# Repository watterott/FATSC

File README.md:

# FATSC
FATSC (FAT Storage Controller) is a SD/USB coprocessor to connect USB memory sticks or SD cards to a microcontroller.

* USB-Host MSD/MSC port
* SD-Card interface
* Real-Time-Clock (RTC)
* FAT/FAT32 file system
* Based on a ST STM32F205 ARM microcontroller
* ALFAT compatible pinout and commands
* **[Documentation on learn.watterott.com](https://learn.watterott.com)**

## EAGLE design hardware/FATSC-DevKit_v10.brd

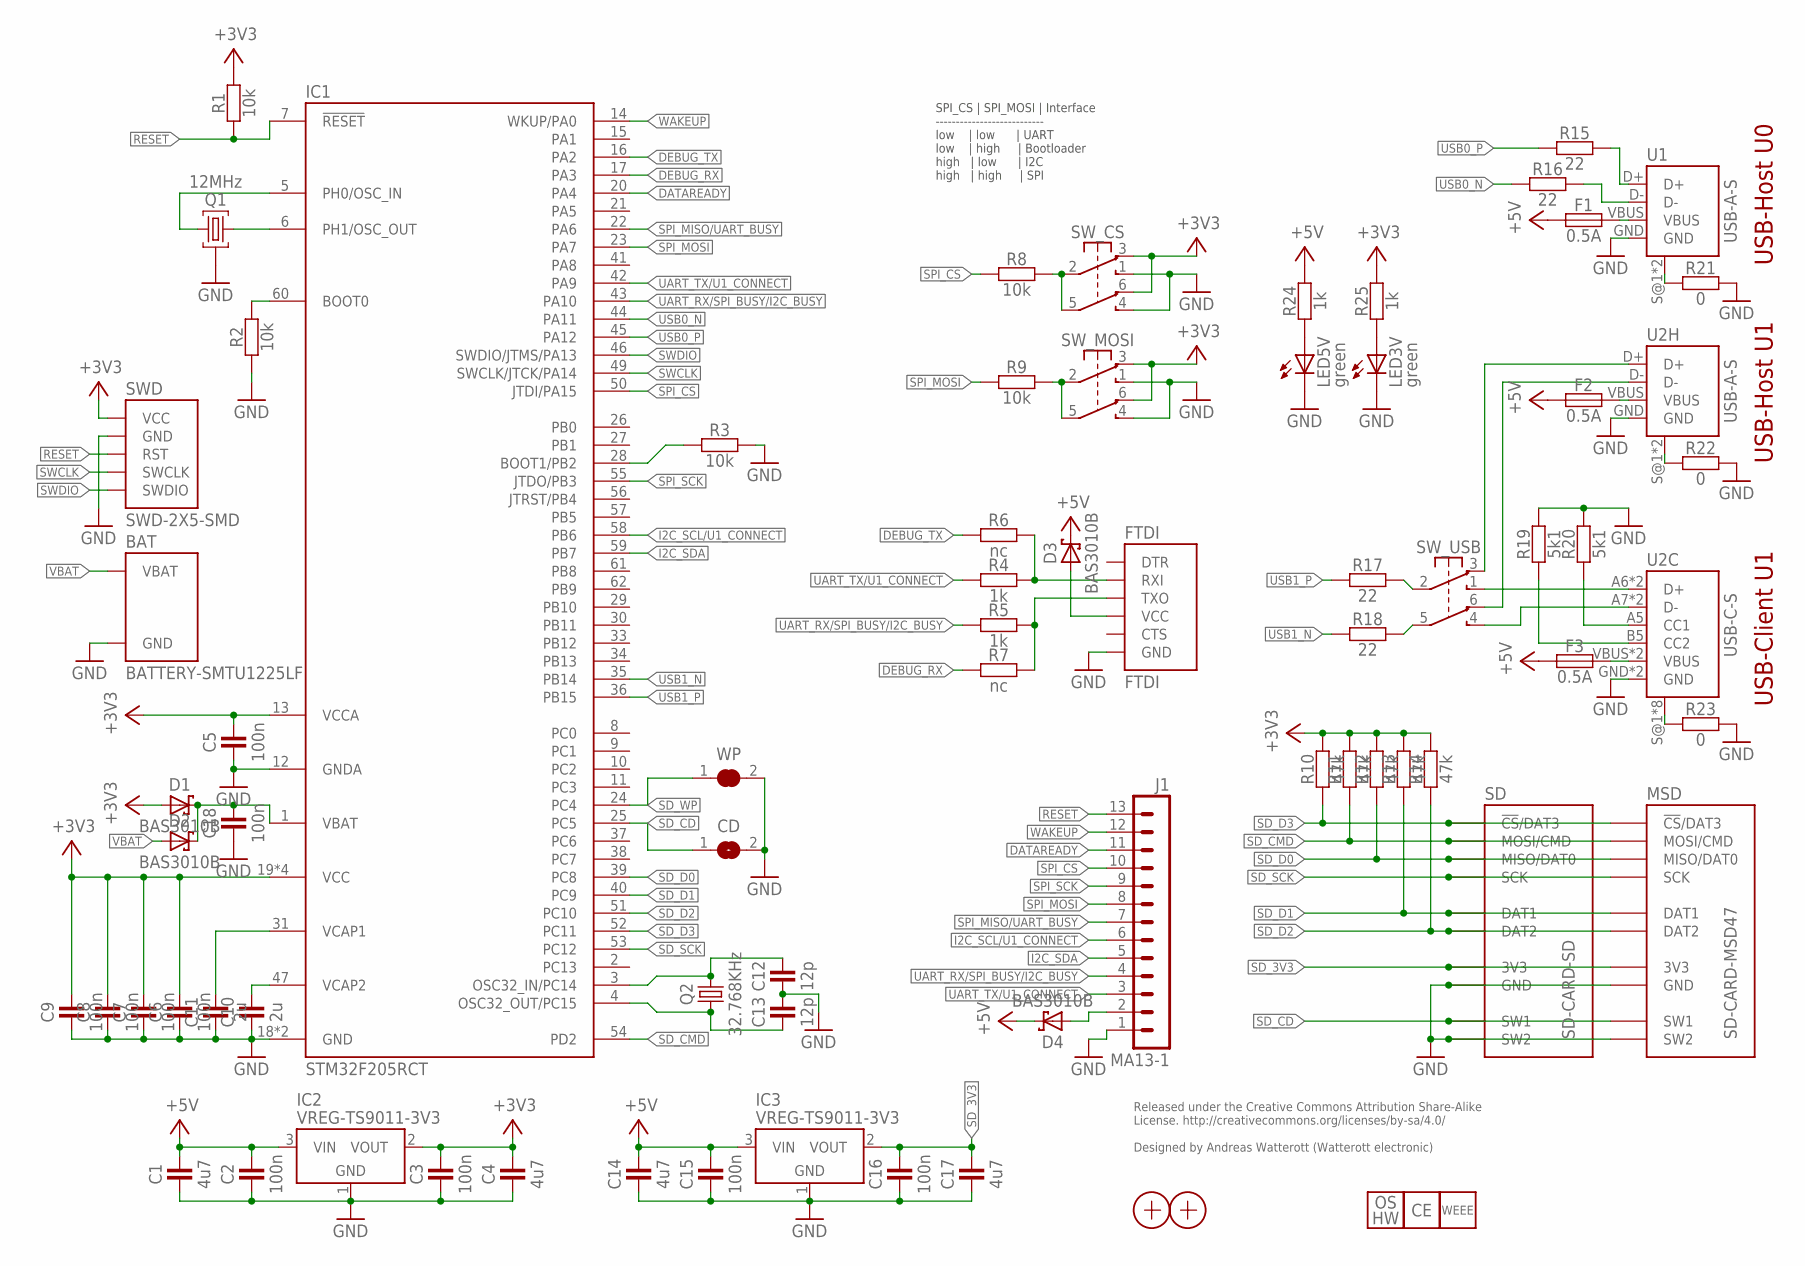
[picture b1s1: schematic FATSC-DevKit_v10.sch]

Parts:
BAT: BATTERY-SMTU1225LF; BAT-SMTU1225LF
C1, C4, C14, C17: 4u7; C0603
C2, C3, C5, C6, C7, C8, C9, C15, C16, C18: 100n; C0603
C10, C11: 2u; C0603
C12, C13: 12p; C0603
CD: JUMPER2-0603-NC; JUMPER2-0603_NC
D1, D2, D3, D4: BAS3010B; SOD323
F1, F2, F3: 0.5A; C0805
FTDI: FTDI
IC1: STM32F205RCT; LQFP64
IC2, IC3: VREG-TS9011-3V3; SOT23
J1: MA13-1
LED3V, LED5V: green; C0603
LOGO7: LOGO_OSHW-4; OSHW_4MM
LOGO8: LOGO_CE-2; CE_2MM
LOGO9: LOGO_WEEE-4; WEEE_4MM
MSD: SD-CARD-MSD47; SD_47309XXXX
Q1: 12MHz; CRYSTAL_32X13
Q2: 32.768KHz; CRYSTAL_ZM315
R1, R2, R3, R8, R9: 10k; C0603
R4, R5, R24, R25: 1k; C0603
R6, R7: nc; C0603
R10, R11, R12, R13, R14: 47k; C0603
R15, R16, R17, R18: 22; C0603
R19, R20: 5k1; C0603
R21, R22, R23: 0; C0603
SD: SD-CARD-SD; SD_SDBMF00915B0T2
SWD: SWD-2X5-SMD; SWD-2X5_SMD
SW_CS: SW-2UM-CUS22B; CUS22B
SW_MOSI: SW-2UM-CUS22B; CUS22B
SW_USB: SW-2UM-CUS22B; CUS22B
U1, U2H: USB-A-S
U2C: USB-C-S
WP: JUMPER2-0603
X1, X2: PASSER-07; PASSER_07MM

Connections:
5VIN: D4.A, J1.2
+3V3: C3.2, C4.2, C5.2, C6.2, C7.2, C8.2, C9.2, D1.A, IC1.13 (VCCA), IC1.19 (VCC), IC1.32 (VCC), IC1.48 (VCC), IC1.64 (VCC), IC2.2 (VOUT), R1.2, R10.2, R11.2, R12.2, R13.2, R14.2, R25.2, SWD.VCC, SW_CS.3 (NC1), SW_CS.6 (NC2), SW_MOSI.3 (NC1), SW_MOSI.6 (NC2)
+5V: C1.2, C2.2, C14.2, C15.2, D3.C, D4.C, F1.1, F2.1, F3.1, IC2.3 (VIN), IC3.3 (VIN), R24.2
BOOT0: IC1.60 (BOOT0), R2.2
BOOT1: IC1.28 (BOOT1/PB2), R3.1
CC1: R20.1, U2C.A5 (CC1)
CC2: R19.1, U2C.B5 (CC2)
CS: R8.2, SW_CS.2 (C1), SW_CS.5 (C2)
D0_N: R16.2, U1.D-
D0_P: R15.2, U1.D+
D1C_N: SW_USB.4 (NO2), U2C.A7 (D-), U2C.B7 (D-)
D1C_P: SW_USB.1 (NO1), U2C.A6 (D+), U2C.B6 (D+)
D1H_N: SW_USB.6 (NC2), U2H.D-
D1H_P: SW_USB.3 (NC1), U2H.D+
D1_N: R18.2, SW_USB.5 (C2)
D1_P: R17.2, SW_USB.2 (C1)
DATAREADY: IC1.20 (PA4), J1.11
DEBUG_RX: IC1.17 (PA3), R7.1
DEBUG_TX: IC1.16 (PA2), R6.1
FTDI_VCC: D3.A, FTDI.3-VCC (VCC)
GND: BAT.- (GND), C1.1, C2.1, C3.1, C4.1, C5.1, C6.1, C7.1, C8.1, C9.1, C10.1, C11.1, C12.1, C13.2, C14.1, C15.1, C16.1, C17.1, C18.1, CD.2, FTDI.1-GND (GND), IC1.12 (GNDA), IC1.18 (GND), IC1.63 (GND), IC2.1 (GND), IC3.1 (GND), J1.1, LED3V.C, LED5V.C, MSD.GND, MSD.GND@1 (GND), MSD.GND@2 (GND), MSD.SW2, Q1.GND, R2.1, R3.2, R19.2, R20.2, R21.2, R22.2, R23.2, SD.GND@1 (GND), SD.GND@2 (GND), SD.GND@3 (GND), SD.SW2, SWD.GND@1 (GND), SWD.GND@2 (GND), SWD.GND@3 (GND), SW_CS.1 (NO1), SW_CS.4 (NO2), SW_MOSI.1 (NO1), SW_MOSI.4 (NO2), U1.GND, U2C.GND, U2C.GND2 (GND), U2H.GND, WP.2
I2C_SCL/U1_CONNECT: IC1.58 (PB6), J1.6
I2C_SDA: IC1.59 (PB7), J1.5
MOSI: R9.2, SW_MOSI.2 (C1), SW_MOSI.5 (C2)
unnamed: LED5V.A, R24.1
unnamed: LED3V.A, R25.1
OSC32I: C12.2, IC1.3 (OSC32_IN/PC14), Q2.2
OSC32O: C13.1, IC1.4 (OSC32_OUT/PC15), Q2.1
OSCI: IC1.5 (PH0/OSC_IN), Q1.2
OSCO: IC1.6 (PH1/OSC_OUT), Q1.1
RESET: IC1.7 (!RESET), J1.13, R1.1, SWD.RST
RXI: FTDI.5-RXI (RXI), R4.2, R6.2
SD_3V3: C16.2, C17.2, IC3.2 (VOUT), MSD.VCC (3V3), SD.VCC (3V3)
SD_CD: CD.1, IC1.25 (PC5), MSD.SW1, SD.SW1
SD_CMD: IC1.54 (PD2), MSD.MOSI (MOSI/CMD), R11.1, SD.MOSI (MOSI/CMD)
SD_D0: IC1.39 (PC8), MSD.MISO (MISO/DAT0), R12.1, SD.MISO (MISO/DAT0)
SD_D1: IC1.40 (PC9), MSD.DAT1, R13.1, SD.DAT1
SD_D2: IC1.51 (PC10), MSD.DAT2, R14.1, SD.DAT2
SD_D3: IC1.52 (PC11), MSD.CS (!CS!/DAT3), R10.1, SD.CS (!CS!/DAT3)
SD_SCK: IC1.53 (PC12), MSD.SCK, SD.SCK
SD_WP: IC1.24 (PC4), WP.1
SPI_CS: IC1.50 (JTDI/PA15), J1.10, R8.1
SPI_MISO/UART_BUSY: IC1.22 (PA6), J1.7
SPI_MOSI: IC1.23 (PA7), J1.8, R9.1
SPI_SCK: IC1.55 (JTDO/PB3), J1.9
SU0: R21.1, U1.S@1 (SHIELD), U1.S@2 (SHIELD)
SU1C: R23.1, U2C.S@1 (SHIELD), U2C.S@2 (SHIELD), U2C.S@3 (SHIELD), U2C.S@4 (SHIELD), U2C.S@5 (SHIELD), U2C.S@6 (SHIELD), U2C.S@7 (SHIELD), U2C.S@8 (SHIELD)
SU1H: R22.1, U2H.S@1 (SHIELD), U2H.S@2 (SHIELD)
SWCLK: IC1.49 (SWCLK/JTCK/PA14), SWD.SWCLK
SWDIO: IC1.46 (SWDIO/JTMS/PA13), SWD.SWDIO
TXO: FTDI.4-TXO (TXO), R5.2, R7.2
UART_RX/SPI_BUSY/I2C_BUSY: IC1.43 (PA10), J1.4, R5.1
UART_TX/U1_CONNECT: IC1.42 (PA9), J1.3, R4.1
USB0_N: IC1.44 (PA11), R16.1
USB0_P: IC1.45 (PA12), R15.1
USB1_N: IC1.35 (PB14), R18.1
USB1_P: IC1.36 (PB15), R17.1
VB: C18.2, D1.C, D2.C, IC1.1 (VBAT)
VBAT: BAT.+ (VBAT), D2.A
VBUS_U0: F1.2, U1.VBUS
VBUS_U1C: F3.2, U2C.VBUS, U2C.VBUS2 (VBUS)
VBUS_U1H: F2.2, U2H.VBUS
VCAP1: C11.2, IC1.31 (VCAP1)
VCAP2: C10.2, IC1.47 (VCAP2)
WAKEUP: IC1.14 (WKUP/PA0), J1.12

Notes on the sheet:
Released under the Creative Commons Attribution Share-Alike License. http://creativecommons.org/licenses/by-sa/4.0/ Designed by Andreas Watterott (Watterott electronic)
USB-Host U0
USB-Host U1
USB-Client U1
SPI_CS | SPI_MOSI | Interface --------------------------- low | low | UART low | high | Bootloader high | low | I2C high | high | SPI

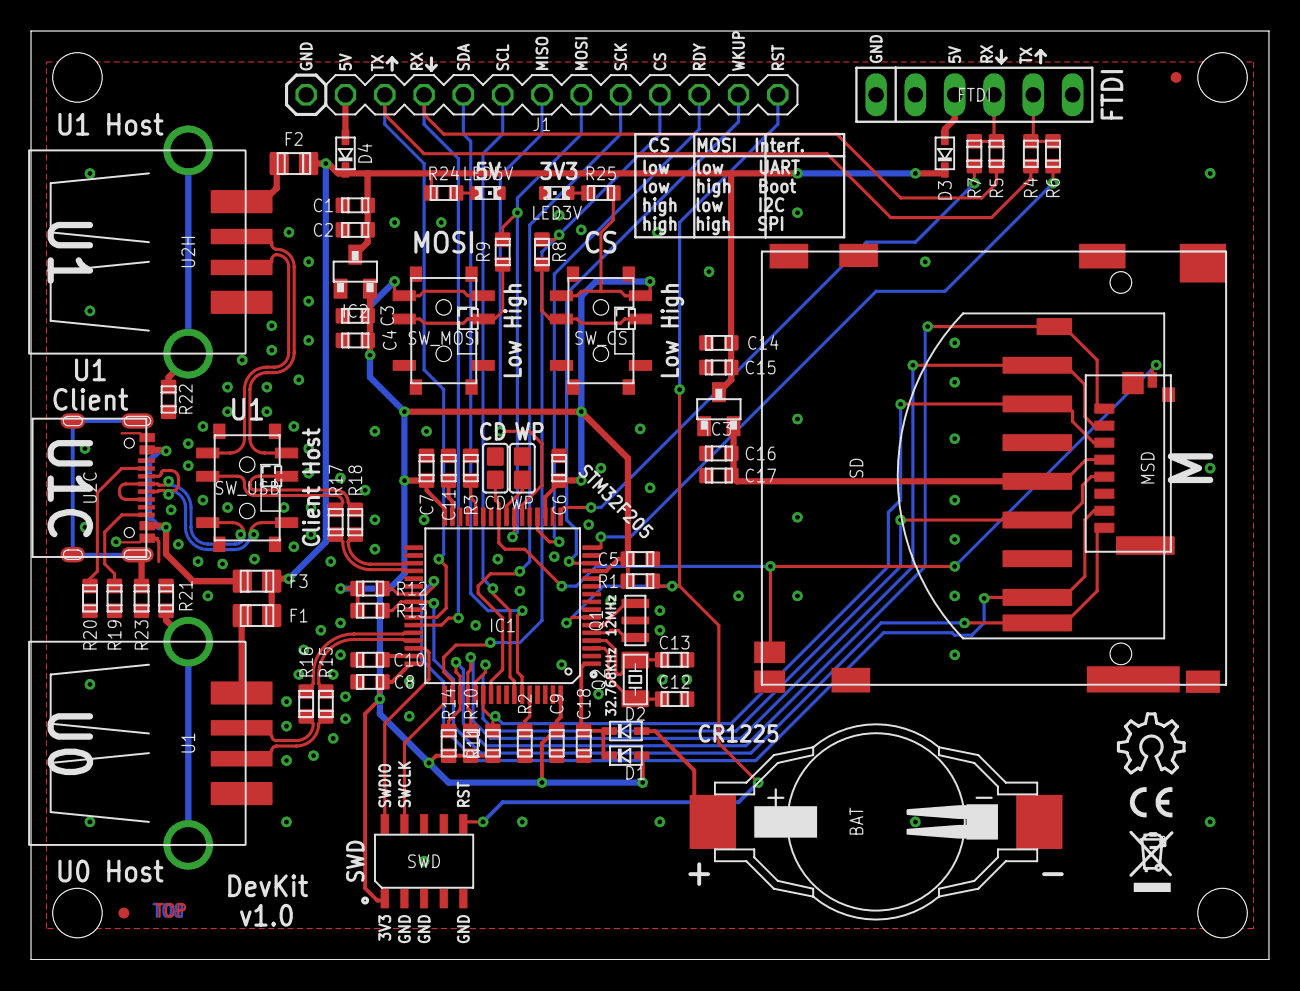
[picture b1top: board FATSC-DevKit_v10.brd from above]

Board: 2 copper layers, 80.0 x 60.0 mm, 76 parts (0 on the bottom side), 65 nets.

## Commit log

2020-09-16 added readme
2020-09-16 added layout and schematics
2020-09-17 added photo
2020-10-17 added examples
2020-10-18 updated SPI example
2020-11-25 updated examples
